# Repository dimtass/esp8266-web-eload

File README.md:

esp8266-web-eload
---
This project is how to build an electronic load with a web interface
by using the esp8266-E12 module and some other electronic components.
This version is using the Arduino ESP8266 for simplicity, but I would
like to make this soon also baremetal and use the ESP API instead.

## Board
You can also find the scematics to build a small pcb for that.
As you may already know, the esp8266 has a 10-bit ADC, but it lacks
a DAC. Therefore, we need an external SPI DAC. You can use any DAC
but as it is a home-project I prefer to use a bit more expensive
components.

The main components I've used are:
* `FDP6030BL`: N-Channel Logic Level MOSFET. This mosfet is features
40A, 30V, Rds(on)=0.024Ω @ Vgs=4.5V, 175oC max junction temp
* `MCP4821`: 12-bit SPI DAC with an internal Vref. This one has an
internal 2.048V reference and a 2x gain, therefore the Vref can be
up to 4.096V with a great accuracy. This means that we can drive the
Vgs on the MOSFET up to 4.096V, which means up to 4A with 1Ω load
resistor. If you need more current, then you can use the `MCP4921`
opamp which has an external reference, but that also means that you
need to provide a very clean and stable reference, too.
* `MCP6H04`: 4x single-supply, rail-to-rail opamp. This IC has four
opamps in the case. One is used to multiply the DAC output by a factor
of 2.2. One is used to drive the MOSFET and another one to buffer
the negative feedback loop to drive the ADC via a low pass RC filter
and a voltage divider with a 1/10 ratio.
* `FT232RL`: A USB to serial IC that is used for two reasons. One
is to power the circuit with 5V from the USB and the other is to
flash the esp8266. You need an IC that also has the DTR/RTS signals
in order to reset the board and put it into flash mode.

The DAC is 12-bit and it can take values 0-2.048V when the gain
is set to 1x or 0-4.096V when the gain is 2x. Also the ADC is 10-bits
with max input voltage 3V3, therefore it has 1024 steps. This means
that you need to use a voltage divider to feed the ADC.

## Build
You need to have the arduino IDE installed. I'm using Linux, so I'm
describing how to do that on Linux. First, download the IDE from
[here](https://www.arduino.cc/en/Main/Software). I usually prefer
specific versions because arduino IDE versions are known to be
incopatible with each other and some commands may not work between
versions. Therefore, for this project prefer to use version `1.8.6`
from [here](https://www.arduino.cc/download_handler.php?f=/arduino-1.8.6-linux64.tar.xz).
This is the x86_64 Linux version.

Extract the contents somewhere. I prefer `/opt`, for example
`/opt/arduino-1.8.6`.

Then open a console and run these commands:
```sh
mkdir -p ~/Arduino/hardware/esp8266com
cd ~/Arduino/hardware/esp8266com
git clone https://github.com/esp8266/Arduino.git esp8266
cd esp8266/tools
python get.py
/opt/arduino-1.8.6/arduino --install-boards esp8266:esp8266 --save-prefs
```

Then run the Arduino IDE and click `Tools -> Manage Libraries` and search
for the `websockets by Markus Sattler` library and select version `2.1.1`.
Then exit the Arduino IDE and from the source code folder run:
```sh
./build.sh
```

If your arduino IDE is not installed in `/opt/arduino-1.8.6` or you're
using a different version then you need to edit the `build.sh` script
and change the `ARDUINO=` variable with the correct path.

If everything goes right then you should have a folder named `build` and
inside that fodler a file named `esp8266-web-eload.ino.bin`.

Then connect you esp8266-E12 board with a USB cable on your computer and
verify which port is enumerated on it
```sh
dmesg | grep tty
```

Usually it will be the last port listed after you run the above command.

Finally, run the `upload-http-files.sh` script with the port you've found:
```sh
./upload-http-files.sh /dev/ttyUSB0
```

You might need to change the paths of the `mkspiffs` and `esptool` for the
script to work properly. If you want to be able to upload the web interface
from the Arduino IDE, then have a look to this plugin [here](https://github.com/esp8266/arduino-esp8266fs-plugin).
This will integrate this functionality in the IDE. I'm using the script
as it flashes everything on one go, but for development you don't have
to upload everything, so if you just change something in the code and the
web interface remains the same or the opposite, then better use the IDE.

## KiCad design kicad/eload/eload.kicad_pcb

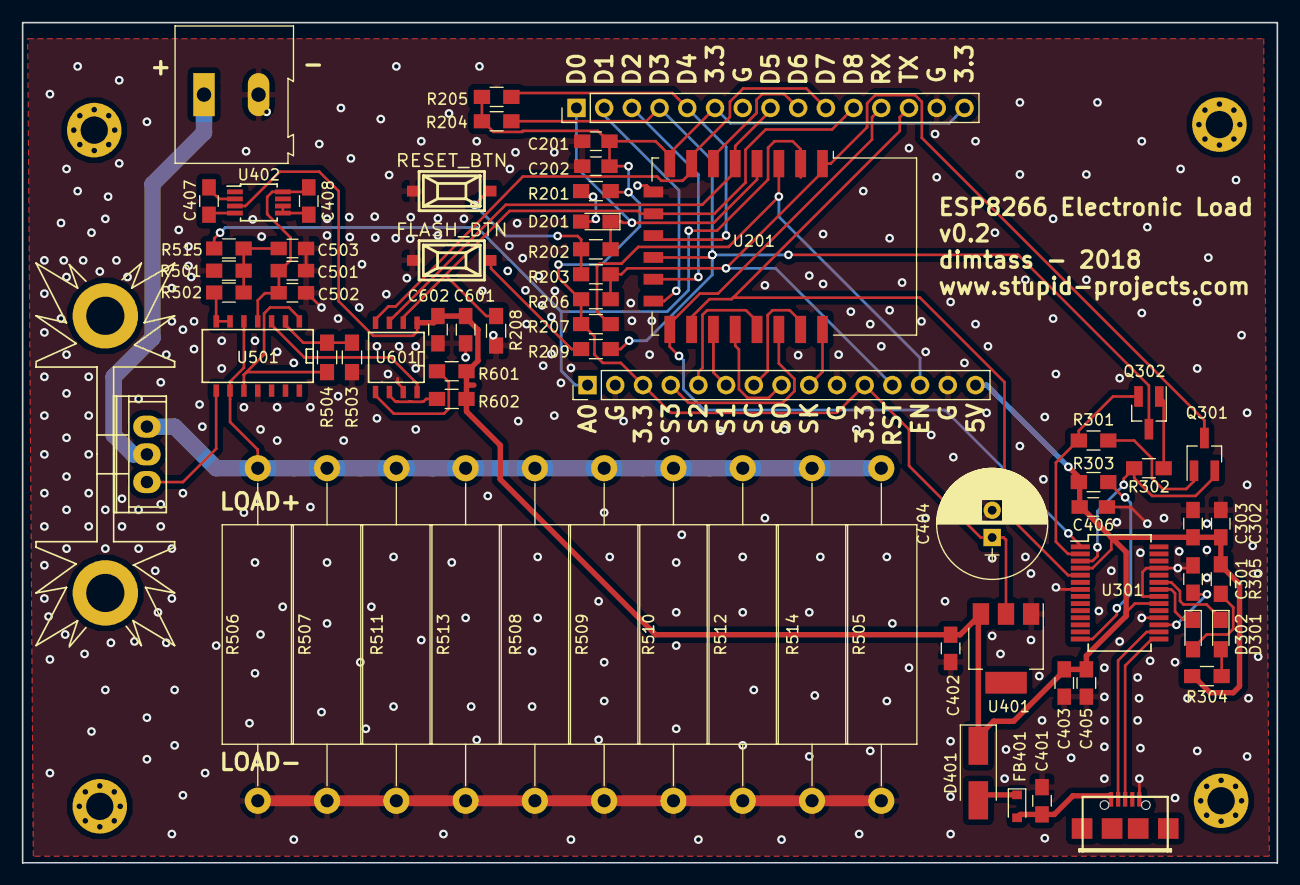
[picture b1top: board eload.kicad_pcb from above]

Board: 2 copper layers, 115.0 x 77.0 mm, 74 parts (0 on the bottom side), 54 nets.

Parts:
C201: 1u; C_0805_HandSoldering
C202, C601: 100n; C_0805_HandSoldering
C301, C302, C403, C501: 100nF; C_0805_HandSoldering
C303, C405, C406, C407, C408, C502, C503: 10uF; C_0805_HandSoldering
C401: 10nF; C_0805_HandSoldering
C402: 10uF 25V; C_0805_HandSoldering
C404: 220uF; CP_Radial_D10.0mm_P2.50mm
C602: 1uF; C_0805_HandSoldering
D201: LED; LED_0805_HandSoldering
D301: TXLED; LED_0805_HandSoldering
D302: RXLED; LED_0805_HandSoldering
D401: LSM115JE3/TR13; D_SMA_Handsoldering
FB401: MH2029-400Y; D_0805
H401, H402, H403, H404: MountingHole; MountingHole_2.5mm_Pad_Via
HS501: Heatsink; Heatsink_Fischer_SK104-STCB_35x13mm__2xDrill3.5mm_ScrewM3
J201, J202: Conn_01x15_Male; Pin_Header_Straight_1x15_Pitch2.54mm
J301: USB_B_Micro; conn_usb_B_micro_smd-3
J501: LOAD; TerminalBlock_Altech_AK300-2_P5.00mm
Q301, Q302: MMBT3904; SOT-23_Handsoldering
Q501: FDP6030BL; TO-220
R201, R203, R209: 470; R_0805_HandSoldering
R202: 0 (NC); R_0805_HandSoldering
R204, R205, R206, R207, R208, R303, R502, R503, R601, R602: 10K; R_0805_HandSoldering
R301, R302, R504: 12K; R_0805_HandSoldering
R304, R305: R; R_0805_HandSoldering
R501: 1K; R_0805_HandSoldering
R505, R506, R507, R508, R509, R510, R511, R512, R513, R514: 10Ω/1W; R_Axial_Power_L20.0mm_W6.4mm_P30.48mm
R515: 15K; R_0805_HandSoldering
SW201: RESET_BTN; smd_push
SW202: FLASH_BTN; smd_push
U201: ESP-12F; ESP-12E
U301: FT232RL; SSOP-28_5.3x10.2mm_Pitch0.65mm
U401: AMS1117-3.3; SOT-223
U402: SP6661; MSOP-8_3x3mm_Pitch0.65mm
U501: MCP6H04; SOIC-14_N
U601: MCP4821; SOIC-8-N

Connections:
+3V3: C201.2, C202.2, C404.1, J201.3, J201.11, J202.6, J202.15, R201.1, R204.2, R205.2, R206.2, R207.2, U201.8, U401.2
+5V: C302.1, C303.1, C402.1, C403.1, C405.1, C406.1, C601.1, C602.1, D401.1, J201.15, R303.1, R304.1, R305.1, R601.1, R602.1, U301.4, U301.20, U401.3, U402.3, U601.1
+10V: C408.1, C501.1, C502.1, U402.8, U501.4
/ESP8266-E12/CH_PD: J201.13, R207.1, U201.3
/ESP8266-E12/ESP_GPIO0: J202.4, Q302.3, R204.1, R209.1, U201.12
/ESP8266-E12/ESP_RXD0: J202.12, U201.15, U301.1
/ESP8266-E12/ESP_SPI_MISO: J202.9, U201.6
/ESP8266-E12/ESP_TXD0: J202.13, U201.16, U301.5
/ESP8266-E12/GPIO2: J202.5, R205.1, U201.11
/ESP8266-E12/GPIO4: J202.3, U201.13
/ESP8266-E12/GPIO5: J202.2, U201.14
/ESP8266-E12/GPIO6: J201.9, U201.22
/ESP8266-E12/GPIO7: J201.8, U201.18
/ESP8266-E12/GPIO8: J201.7, U201.21
/ESP8266-E12/GPIO9: J201.5, U201.19
/ESP8266-E12/GPIO10: J201.4, U201.20
/ESP8266-E12/GPIO11: J201.6, U201.17
/ESP8266-E12/GPIO16: D201.1, J202.1, R202.1, U201.4
/OPAMPS and MOSFET/ADC_OUT: J201.1, R515.2, U201.2
/OPAMPS and MOSFET/DAC_IN: U501.3, U601.8
/USB to UART/DTR: Q302.2, R301.2, U301.2
/USB to UART/D_N: J301.2, U301.16
/USB to UART/D_P: J301.3, U301.15
/USB to UART/ESP_RESET: J201.12, Q301.3, R203.1, R206.1, U201.1
/USB to UART/RTS: Q301.2, R302.2, U301.3
/external DAC/DAC_SPI_CLK: J202.8, U201.5, U601.3
/external DAC/DAC_SPI_CS: J202.11, R208.1, U201.10, U601.2
/external DAC/DAC_SPI_DI: J202.10, U201.7, U601.4
GND: C201.1, C202.1, C301.2, C302.2, C303.2, C401.2, C402.2, C403.2, C404.2, C405.2, C406.2, C501.2, C502.2, C503.2, C601.2, C602.2, J201.2, J201.10, J201.14, J202.7, J202.14, J301.5, J501.2, R208.2, R501.1, R503.2, R505.2, R506.2, R507.2, R508.2, R509.2, R510.2, R511.2, R512.2, R513.2, R514.2, SW201.2, SW202.2, U201.9, U301.7, U301.18, U301.21, U301.25, U401.1, U501.11, U601.7
unnamed: C301.1, U301.17
unnamed: C407.1, U402.2
unnamed: C407.2, U402.4
unnamed: C408.2, U402.5, U402.6
unnamed: C503.1, R501.2, R502.2, R515.1
unnamed: D201.2, R201.2
unnamed: D301.1, U301.23
unnamed: D301.2, R304.2
unnamed: D302.1, U301.22
unnamed: D302.2, R305.2
unnamed: D401.2, FB401.1
unnamed: J501.1, Q501.2
unnamed: Q301.1, R301.1
unnamed: Q302.1, R302.1
unnamed: Q501.1, U501.8
unnamed: Q501.3, R505.1, R506.1, R507.1, R508.1, R509.1, R510.1, R511.1, R512.1, R513.1, R514.1, U501.5, U501.9
unnamed: R202.2, R203.2, SW201.1
unnamed: R209.2, SW202.1
unnamed: R303.2, U301.14
unnamed: R502.1, U501.6, U501.7
unnamed: R503.1, R504.2, U501.2
unnamed: R504.1, U501.1, U501.10
unnamed: R601.2, U601.5
unnamed: R602.2, U601.6
VBUS: C401.1, FB401.2, J301.1

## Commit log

2018-11-25 modifications
2018-11-25 Edited README
2018-11-26 Updated files
2018-12-03 Added kicad schematics
2018-12-03 kicad libraries change
2018-12-20 Version 0.2
2018-12-20 Added an RC filter in the ADC input
2018-12-20 Moved block terminal on top
2018-12-20 Convert adc points to volts
2018-12-20 Updated script
2018-12-20 Bug fixes
